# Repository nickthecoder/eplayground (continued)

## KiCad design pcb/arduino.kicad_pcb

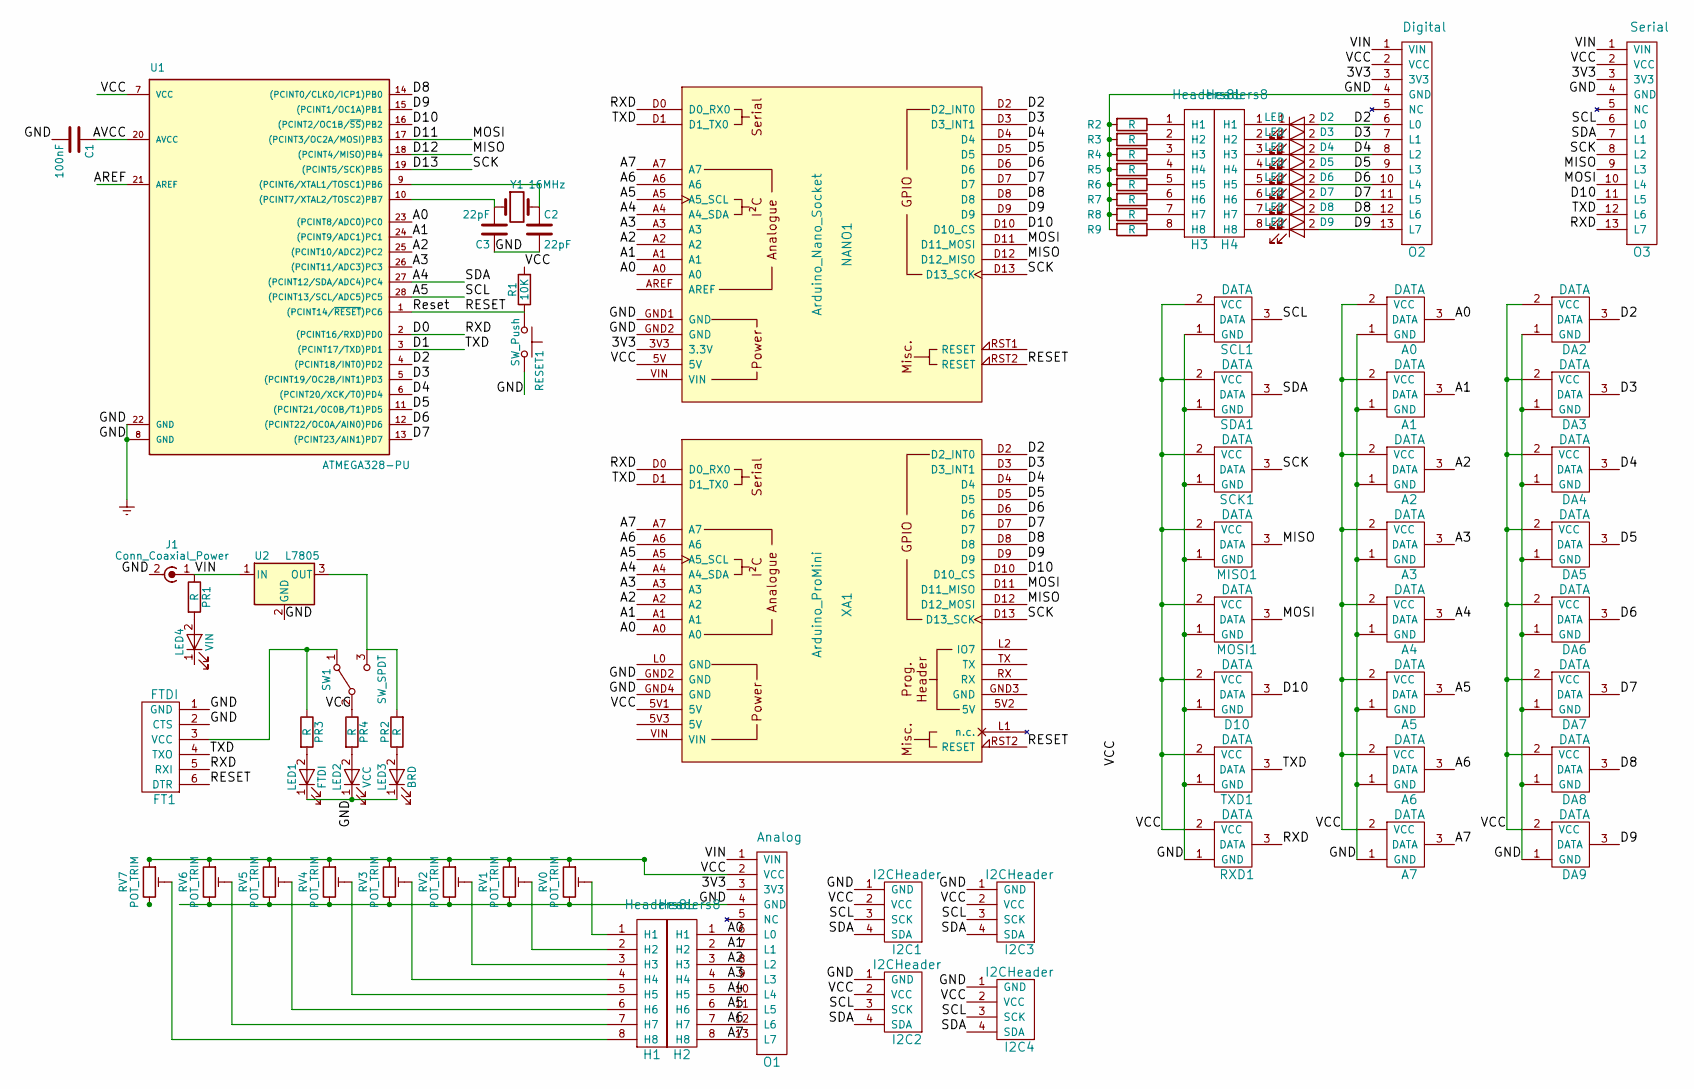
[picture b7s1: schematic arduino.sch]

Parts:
A0, A1, A2, A3, A4, A5, A6, A7: DATA; Pin_Header_Straight_1x03_Pitch2.54mm
C1: 100nF; C_Disc_D3.0mm_W1.6mm_P2.50mm
C2, C3: 22pF; C_Disc_D3.0mm_W1.6mm_P2.50mm
D2, D3, D4, D5, D6, D7, D8, D9: LED; LED_Rectangular_W5.0mm_H2.0mm
D10: DATA; Pin_Header_Straight_1x03_Pitch2.54mm
DA2, DA3, DA4, DA5, DA6, DA7, DA8, DA9: DATA; Pin_Header_Straight_1x03_Pitch2.54mm
FT1: FTDI; Pin_Header_Straight_1x06_Pitch2.54mm
H1, H3: Headers8L; Pin_Header_Straight_1x08_Pitch2.54mm
H2, H4: Headers8; Pin_Header_Straight_1x08_Pitch2.54mm
I2C1, I2C2, I2C3, I2C4: I2CHeader; Pin_Header_Straight_1x04_Pitch2.54mm
J1: Conn_Coaxial_Power; BARREL_JACK
LED1: FTDI; LED_D3.0mm
LED2: VCC; LED_D3.0mm
LED3: BRD; LED_D3.0mm
LED4: VIN; LED_D3.0mm
MISO1: DATA; Pin_Header_Straight_1x03_Pitch2.54mm
MOSI1: DATA; Pin_Header_Straight_1x03_Pitch2.54mm
NANO1: Arduino_Nano_Socket; Arduino_Nano
O1: Analog; Pin_Header_Straight_1x13_Pitch2.54mm
O2: Digital; Pin_Header_Straight_1x13_Pitch2.54mm
O3: Serial; Pin_Header_Straight_1x13_Pitch2.54mm
PR1, PR2, PR3, PR4: R; R_Axial_DIN0204_L3.6mm_D1.6mm_P5.08mm_Horizontal
R1: 10K; R_Axial_DIN0204_L3.6mm_D1.6mm_P5.08mm_Horizontal
R2, R3, R4, R5, R6, R7, R8, R9: R; R_Axial_DIN0204_L3.6mm_D1.6mm_P5.08mm_Horizontal
RESET1: SW_Push; SW_PUSH_6mm
RV0, RV1, RV2, RV3, RV4, RV5, RV6, RV7: POT_TRIM; Potentiometer_Trimmer_Piher_PT-6v_Horizontal
RXD1: DATA; Pin_Header_Straight_1x03_Pitch2.54mm
SCK1: DATA; Pin_Header_Straight_1x03_Pitch2.54mm
SCL1: DATA; Pin_Header_Straight_1x03_Pitch2.54mm
SDA1: DATA; Pin_Header_Straight_1x03_Pitch2.54mm
SW1: SW_SPDT; SW_CuK_JS202011CQN_DPDT_Straight
TXD1: DATA; Pin_Header_Straight_1x03_Pitch2.54mm
U1: ATMEGA328-PU; DIP-28_W7.62mm
U2: L7805; TO-220
XA1: Arduino_ProMini; Arduino_ProMini_NoFTDI
Y1: 16MHz; Resonator-2pin_w6.0mm_h3.0mm

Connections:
/3V3: NANO1.3V3 (3.3V), O1.3 (3V3), O2.3 (3V3), O3.3 (3V3)
/A0: A0.3 (DATA), H2.1 (H1), NANO1.A0, O1.6 (L0), U1.23 ((PCINT8/ADC0)PC0), XA1.A0
/A1: A1.3 (DATA), H2.2 (H2), NANO1.A1, O1.7 (L1), U1.24 ((PCINT9/ADC1)PC1), XA1.A1
/A2: A2.3 (DATA), H2.3 (H3), NANO1.A2, O1.8 (L2), U1.25 ((PCINT10/ADC2)PC2), XA1.A2
/A3: A3.3 (DATA), H2.4 (H4), NANO1.A3, O1.9 (L3), U1.26 ((PCINT11/ADC3)PC3), XA1.A3
/A4: A4.3 (DATA), H2.5 (H5), I2C1.4 (SDA), I2C2.4 (SDA), I2C3.4 (SDA), I2C4.4 (SDA), NANO1.A4 (A4_SDA), O1.10 (L4), O3.7 (L1), SDA1.3 (DATA), U1.27 ((PCINT12/SDA/ADC4)PC4), XA1.A4 (A4_SDA)
/A5: A5.3 (DATA), H2.6 (H6), I2C1.3 (SCK), I2C2.3 (SCK), I2C3.3 (SCK), I2C4.3 (SCK), NANO1.A5 (A5_SCL), O1.11 (L5), O3.6 (L0), SCL1.3 (DATA), U1.28 ((PCINT13/SCL/ADC5)PC5), XA1.A5 (A5_SCL)
/A6: A6.3 (DATA), H2.7 (H7), NANO1.A6, O1.12 (L6), XA1.A6
/A7: A7.3 (DATA), H2.8 (H8), NANO1.A7, O1.13 (L7), XA1.A7
/AVCC: C1.1, U1.20 (AVCC)
/D0: FT1.5 (RXI), NANO1.D0 (D0_RX0), O3.13 (L7), RXD1.3 (DATA), U1.2 ((PCINT16/RXD)PD0), XA1.D0 (D0_RX0)
/D1: FT1.4 (TXO), NANO1.D1 (D1_TX0), O3.12 (L6), TXD1.3 (DATA), U1.3 ((PCINT17/TXD)PD1), XA1.D1 (D1_TX0)
/D2: D2.2 (A), DA2.3 (DATA), NANO1.D2 (D2_INT0), O2.6 (L0), U1.4 ((PCINT18/INT0)PD2), XA1.D2 (D2_INT0)
/D3: D3.2 (A), DA3.3 (DATA), NANO1.D3 (D3_INT1), O2.7 (L1), U1.5 ((PCINT19/OC2B/INT1)PD3), XA1.D3 (D3_INT1)
/D4: D4.2 (A), DA4.3 (DATA), NANO1.D4, O2.8 (L2), U1.6 ((PCINT20/XCK/T0)PD4), XA1.D4
/D5: D5.2 (A), DA5.3 (DATA), NANO1.D5, O2.9 (L3), U1.11 ((PCINT21/OC0B/T1)PD5), XA1.D5
/D6: D6.2 (A), DA6.3 (DATA), NANO1.D6, O2.10 (L4), U1.12 ((PCINT22/OC0A/AIN0)PD6), XA1.D6
/D7: D7.2 (A), DA7.3 (DATA), NANO1.D7, O2.11 (L5), U1.13 ((PCINT23/AIN1)PD7), XA1.D7
/D8: D8.2 (A), DA8.3 (DATA), NANO1.D8, O2.12 (L6), U1.14 ((PCINT0/CLKO/ICP1)PB0), XA1.D8
/D9: D9.2 (A), DA9.3 (DATA), NANO1.D9, O2.13 (L7), U1.15 ((PCINT1/OC1A)PB1), XA1.D9
/D10: D10.3 (DATA), NANO1.D10 (D10_CS), O3.11 (L5), U1.16 ((PCINT2/OC1B/~SS~)PB2), XA1.D10 (D10_CS)
/D11: MOSI1.3 (DATA), NANO1.D11 (D11_MOSI), O3.10 (L4), U1.17 ((PCINT3/OC2A/MOSI)PB3), XA1.D11 (D11_MISO)
/D12: MISO1.3 (DATA), NANO1.D12 (D12_MISO), O3.9 (L3), U1.18 ((PCINT4/MISO)PB4), XA1.D12 (D12_MOSI)
/D13: NANO1.D13 (D13_SCK), O3.8 (L2), SCK1.3 (DATA), U1.19 ((PCINT5/SCK)PB5), XA1.D13 (D13_SCK)
/RESET: FT1.6 (DTR), NANO1.RST2 (RESET), R1.1, RESET1.1, U1.1 ((PCINT14/~RESET~)PC6), XA1.RST2 (RESET)
/VCC: A0.2 (VCC), A1.2 (VCC), A2.2 (VCC), A3.2 (VCC), A4.2 (VCC), A5.2 (VCC), A6.2 (VCC), A7.2 (VCC), D10.2 (VCC), DA2.2 (VCC), DA3.2 (VCC), DA4.2 (VCC), DA5.2 (VCC), DA6.2 (VCC), DA7.2 (VCC), DA8.2 (VCC), DA9.2 (VCC), I2C1.2 (VCC), I2C2.2 (VCC), I2C3.2 (VCC), I2C4.2 (VCC), MISO1.2 (VCC), MOSI1.2 (VCC), NANO1.5V, O1.2 (VCC), O2.2 (VCC), O3.2 (VCC), PR4.1, R1.2, RV0.1, RV1.1, RV2.1, RV3.1, RV4.1, RV5.1, RV6.1, RV7.1, RXD1.2 (VCC), SCK1.2 (VCC), SCL1.2 (VCC), SDA1.2 (VCC), SW1.2 (B), TXD1.2 (VCC), U1.7 (VCC), XA1.5V1 (5V)
/VIN: J1.1 (In), O1.1 (VIN), O2.1 (VIN), O3.1 (VIN), PR1.1, U2.1 (IN)
Earth: A0.1 (GND), A1.1 (GND), A2.1 (GND), A3.1 (GND), A4.1 (GND), A5.1 (GND), A6.1 (GND), A7.1 (GND), C1.2, C2.2, C3.1, D10.1 (GND), DA2.1 (GND), DA3.1 (GND), DA4.1 (GND), DA5.1 (GND), DA6.1 (GND), DA7.1 (GND), DA8.1 (GND), DA9.1 (GND), FT1.1 (GND), FT1.2 (CTS), I2C1.1 (GND), I2C2.1 (GND), I2C3.1 (GND), I2C4.1 (GND), J1.2 (Ext), LED1.1 (K), LED2.1 (K), LED3.1 (K), MISO1.1 (GND), MOSI1.1 (GND), NANO1.GND1 (GND), NANO1.GND2 (GND), O1.4 (GND), O2.4 (GND), O3.4 (GND), R2.2, R3.2, R4.2, R5.2, R6.2, R7.2, R8.2, R9.2, RESET1.2, RV0.3, RV1.3, RV2.3, RV3.3, RV4.3, RV5.3, RV6.3, RXD1.1 (GND), SCK1.1 (GND), SCL1.1 (GND), SDA1.1 (GND), TXD1.1 (GND), U1.8 (GND), U1.22 (GND), U2.2 (GND), XA1.GND2 (GND), XA1.GND4 (GND)
unnamed: C2.1, U1.9 ((PCINT6/XTAL1/TOSC1)PB6), Y1.2
unnamed: C3.2, U1.10 ((PCINT7/XTAL2/TOSC2)PB7), Y1.1
unnamed: D2.1 (K), H4.1 (H1)
unnamed: D3.1 (K), H4.2 (H2)
unnamed: D4.1 (K), H4.3 (H3)
unnamed: D5.1 (K), H4.4 (H4)
unnamed: D6.1 (K), H4.5 (H5)
unnamed: D7.1 (K), H4.6 (H6)
unnamed: D8.1 (K), H4.7 (H7)
unnamed: D9.1 (K), H4.8 (H8)
unnamed: FT1.3 (VCC), PR3.1, SW1.1 (A)
unnamed: H1.1 (H1), RV0.2
unnamed: H1.2 (H2), RV1.2
unnamed: H1.3 (H3), RV2.2
unnamed: H1.4 (H4), RV3.2
unnamed: H1.5 (H5), RV4.2
unnamed: H1.6 (H6), RV5.2
unnamed: H1.7 (H7), RV6.2
unnamed: H1.8 (H8), RV7.2
unnamed: H3.1 (H1), R2.1
unnamed: H3.2 (H2), R3.1
unnamed: H3.3 (H3), R4.1
unnamed: H3.4 (H4), R5.1
unnamed: H3.5 (H5), R6.1
unnamed: H3.6 (H6), R7.1
unnamed: H3.7 (H7), R8.1
unnamed: H3.8 (H8), R9.1
unnamed: LED1.2 (A), PR3.2
unnamed: LED2.2 (A), PR4.2
unnamed: LED3.2 (A), PR2.1
unnamed: LED4.2 (A), PR1.2
unnamed: PR2.2, SW1.3 (C), U2.3 (OUT)

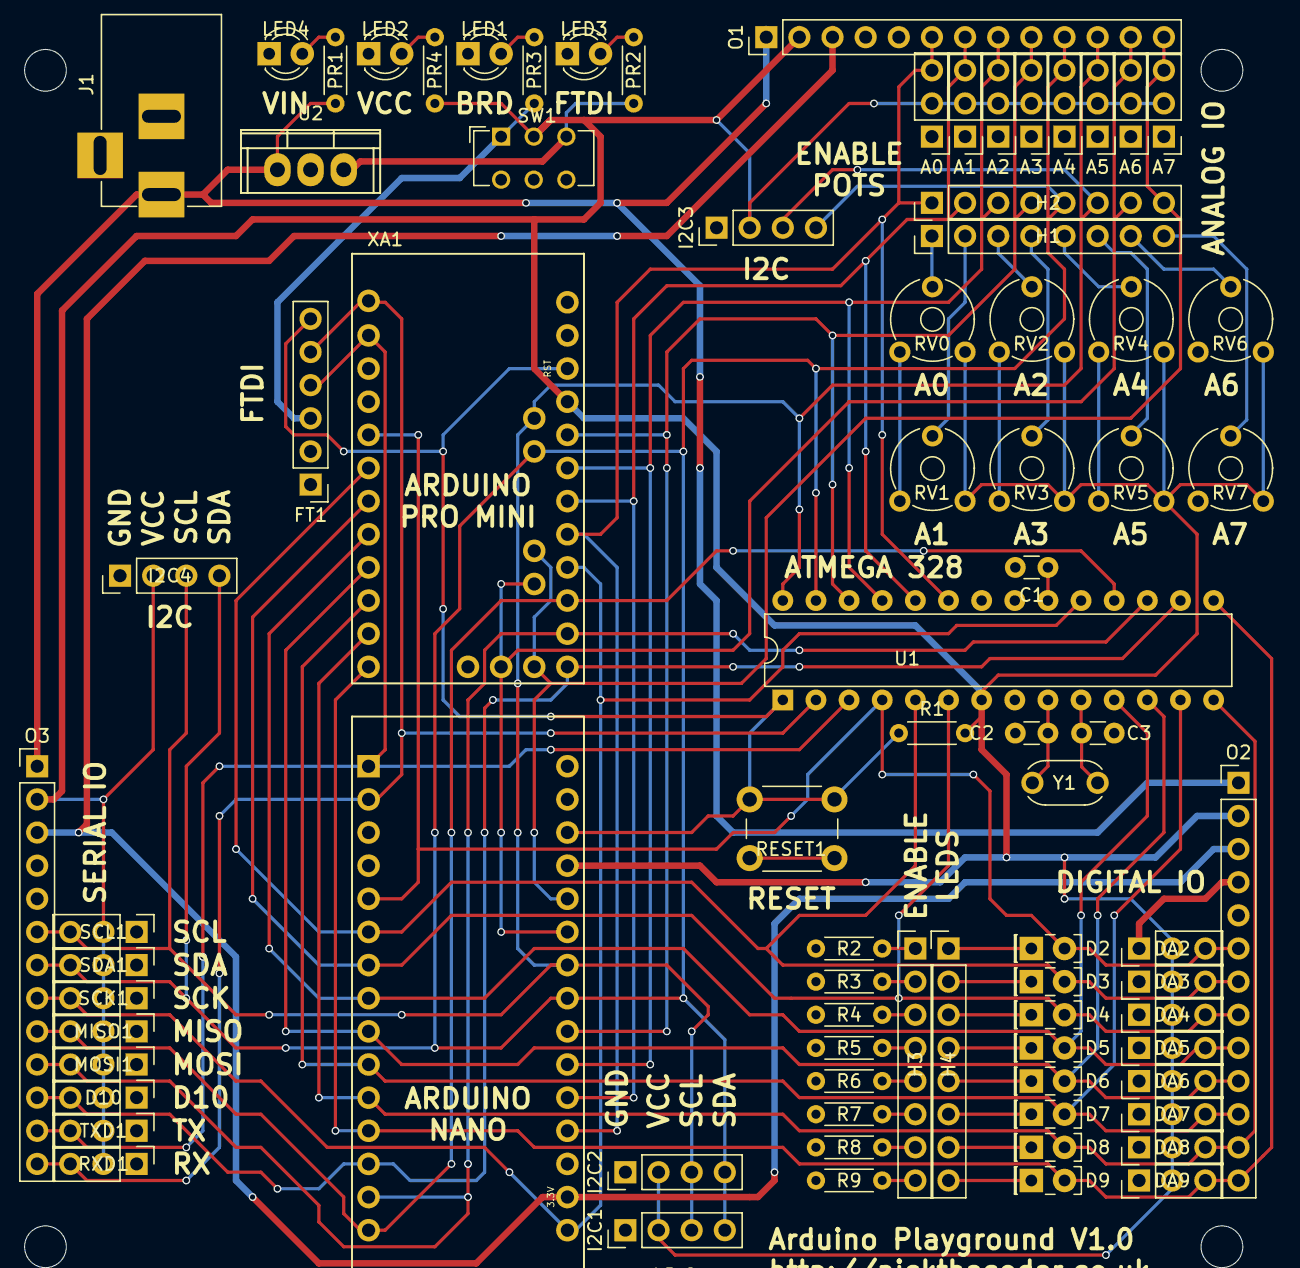
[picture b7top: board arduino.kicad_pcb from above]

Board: 2 copper layers, 80 parts (0 on the bottom side), 60 nets.
